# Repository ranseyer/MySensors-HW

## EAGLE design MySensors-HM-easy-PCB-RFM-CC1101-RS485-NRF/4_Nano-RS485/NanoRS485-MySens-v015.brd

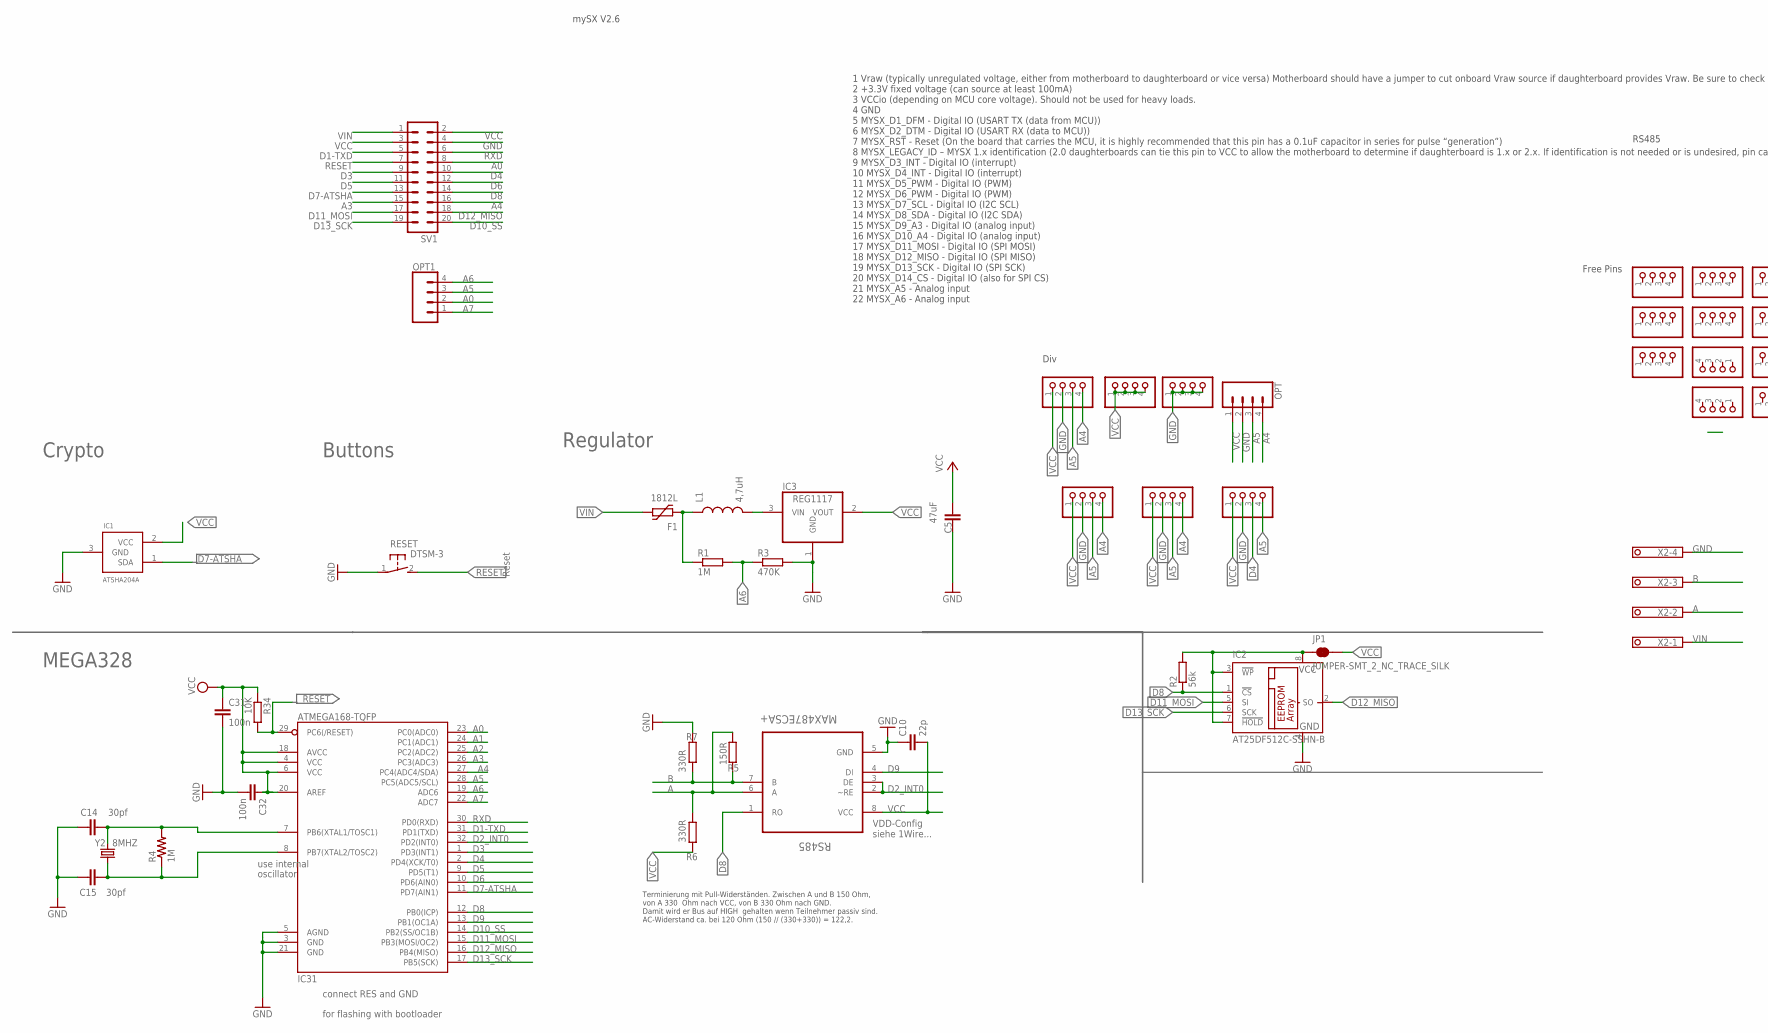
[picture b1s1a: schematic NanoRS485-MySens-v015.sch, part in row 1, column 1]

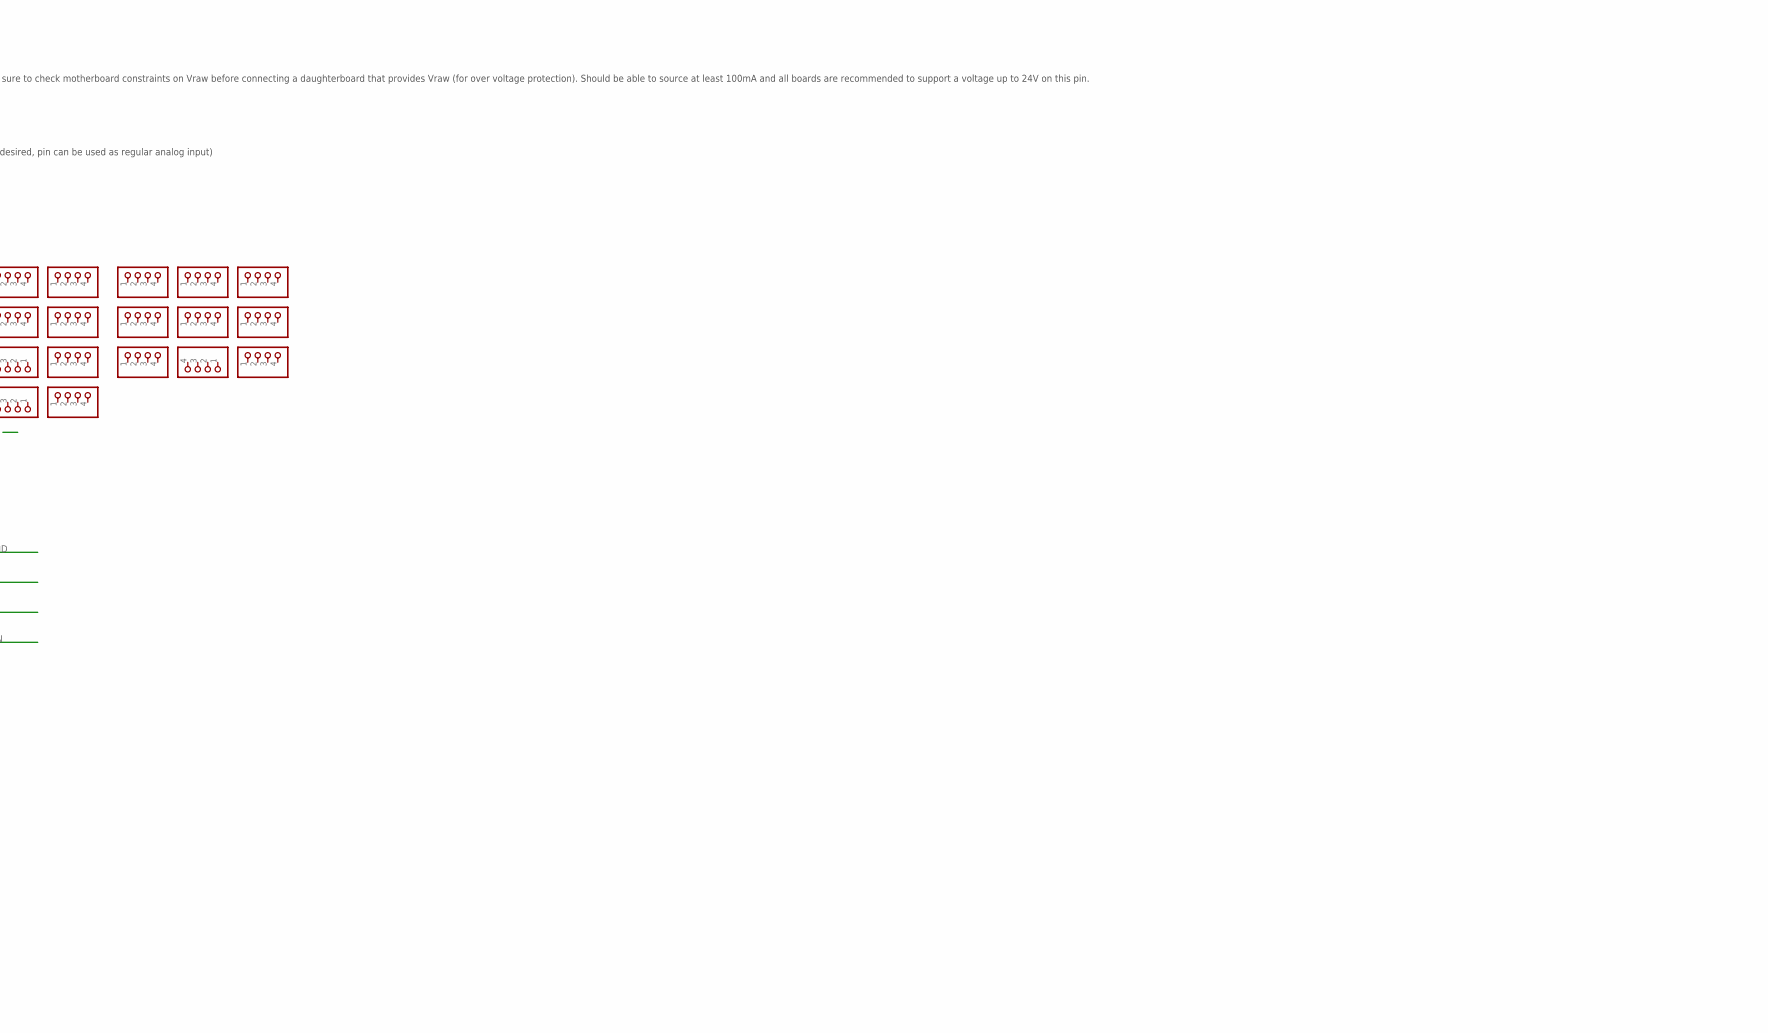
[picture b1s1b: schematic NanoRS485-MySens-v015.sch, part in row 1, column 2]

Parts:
BH1750: PINHD-1X04_2.54-S; 1X04-S
C5: 47uF; C1210
C10: 22p; C0805
C14, C15: 30pf; 0805
C31, C32: 100n; C0805
F1: 1812L
I2C-1, I2C-2: PINHD-1X04_2.54-S; 1X04-S
IC1: ATSHA204A; SOT23
IC2: AT25DF512C-SSHN-B; SO-08
IC3: REG1117; SOT223
IC31: ATMEGA168-TQFP; TQFP32-08
JP1: JUMPER-SMT_2_NC_TRACE_SILK; SMT-JUMPER_2_NC_TRACE_SILK
JP2, JP3, JP4, JP5, JP6, JP7, JP8, JP9, JP10, JP11, JP12, JP13, JP14, JP15, JP16, JP17, JP18, JP19, JP20, JP21, JP22, JP23: PINHD-1X04_2.54-S; 1X04-S
L1: 4,7uH; 0805
MOTION: PINHD-1X04_2.54-S; 1X04-S
OPT, OPT1: CONN_04; 1X04
R1: 1M; R0805
R2: 56k; M0805
R3: 470K; R0805
R4: 1M; 0805
R5: 150R; R0805
R6, R7: 330R; R0805
R34: 10K; R0805
RESET: DTSM-3
RS485: MAX487ECSA+; SOIC127P600X175-8N
SV1: MA10-2
X2: 1751264
Y2: 8MHZ; CRYSTAL-TXC-7A

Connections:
A: R5.1, R6.2, RS485.6 (A), X2.2
A0: IC31.23 (PC0(ADC0)), OPT1.2, SV1.8
A1: IC31.24 (PC1(ADC1))
A2: IC31.25 (PC2(ADC2))
A3: IC31.26 (PC3(ADC3)), SV1.15
A4: BH1750.4, I2C-1.4, I2C-2.4, IC31.27 (PC4(ADC4/SDA)), OPT.4, SV1.16
A5: BH1750.3, I2C-1.3, I2C-2.3, IC31.28 (PC5(ADC5/SCL)), MOTION.4, OPT.3, OPT1.3
A6: IC31.19 (ADC6), OPT1.4, R1.2, R3.1
A7: IC31.22 (ADC7), OPT1.1
B: R5.2, R7.1, RS485.7 (B), X2.3
D1-TXD: IC31.31 (PD1(TXD)), SV1.5
D2_INT0: IC31.32 (PD2(INT0)), RS485.2 (~RE), RS485.3 (DE)
D3: IC31.1 (PD3(INT1)), SV1.9
D4: IC31.2 (PD4(XCK/T0)), MOTION.3, SV1.10
D5: IC31.9 (PD5(T1)), SV1.11
D6: IC31.10 (PD6(AIN0)), SV1.12
D7-ATSHA: IC1.1 (SDA), IC31.11 (PD7(AIN1)), SV1.13
D8: IC2.1 (!CS), IC31.12 (PB0(ICP)), R2.1, RS485.1 (RO), SV1.14
D9: IC31.13 (PB1(OC1A)), RS485.4 (DI)
D10_SS: IC31.14 (PB2(SS/OC1B)), SV1.20
D11_MOSI: IC2.5 (SI), IC31.15 (PB3(MOSI/OC2)), SV1.17
D12_MISO: IC2.2 (SO), IC31.16 (PB4(MISO)), SV1.18
D13_SCK: IC2.6 (SCK), IC31.17 (PB5(SCK)), SV1.19
GND: BH1750.2, C5.1, C10.1, C14.1, C15.1, C31.2, C32.2, I2C-1.2, I2C-2.2, IC1.3 (GND), IC2.4 (GND), IC3.1 (GND), IC31.3 (GND), IC31.5 (AGND), IC31.21 (GND), JP2.1, JP2.2, JP2.3, JP2.4, MOTION.2, OPT.2, R3.2, R7.2, RESET.1, RS485.5 (GND), SV1.4, X2.4
unnamed: C14.2, IC31.7 (PB6(XTAL1/TOSC1)), R4.2, Y2.P$2 (2)
unnamed: C15.2, IC31.8 (PB7(XTAL2/TOSC2)), R4.1, Y2.P$1 (1)
RAW: IC3.3 (VIN), L1.2
RESET: IC31.29 (PC6(/RESET)), R34.2, RESET.2, SV1.7
RXD: IC31.30 (PD0(RXD)), SV1.6
VCC: BH1750.1, C5.2, C10.2, C31.1, C32.1, I2C-1.1, I2C-2.1, IC1.2 (VCC), IC3.2 (VOUT), IC31.4 (VCC), IC31.6 (VCC), IC31.18 (AVCC), IC31.20 (AREF), JP1.2, JP3.1, JP3.2, JP3.3, JP3.4, MOTION.1, OPT.1, R6.1, R34.1, RS485.8 (VCC), SV1.2, SV1.3
VCC1: IC2.3 (!WP), IC2.7 (!HOLD), IC2.8 (VCC), JP1.1, R2.2
VIN: F1.P$2 (2), SV1.1, X2.1
VIN-FUSED: F1.P$1 (1), L1.1, R1.1

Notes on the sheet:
MEGA328
use internal
oscillator
connect RES and GND
for flashing with bootloader
Reset
Crypto
Buttons
Regulator
RS485
VDD-Config siehe 1Wire...
Terminierung mit Pull-Widerständen. Zwischen A und B 150 Ohm, von A 330 Ohm nach VCC, von B 330 Ohm nach GND. Damit wird er Bus auf HIGH gehalten wenn Teilnehmer passiv sind. AC-Widerstand ca. bei 120 Ohm (150 // (330+330)) = 122,2.
1 Vraw (typically unregulated voltage, either from motherboard to daughterboard or vice versa) Motherboard should have a jumper to cut onboard Vraw source if daughterboard provides Vraw. Be sure to check motherboard constraints on Vraw before connecting a daughterboard that provides Vraw (for over 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
mySX V2.6
Div
Free Pins

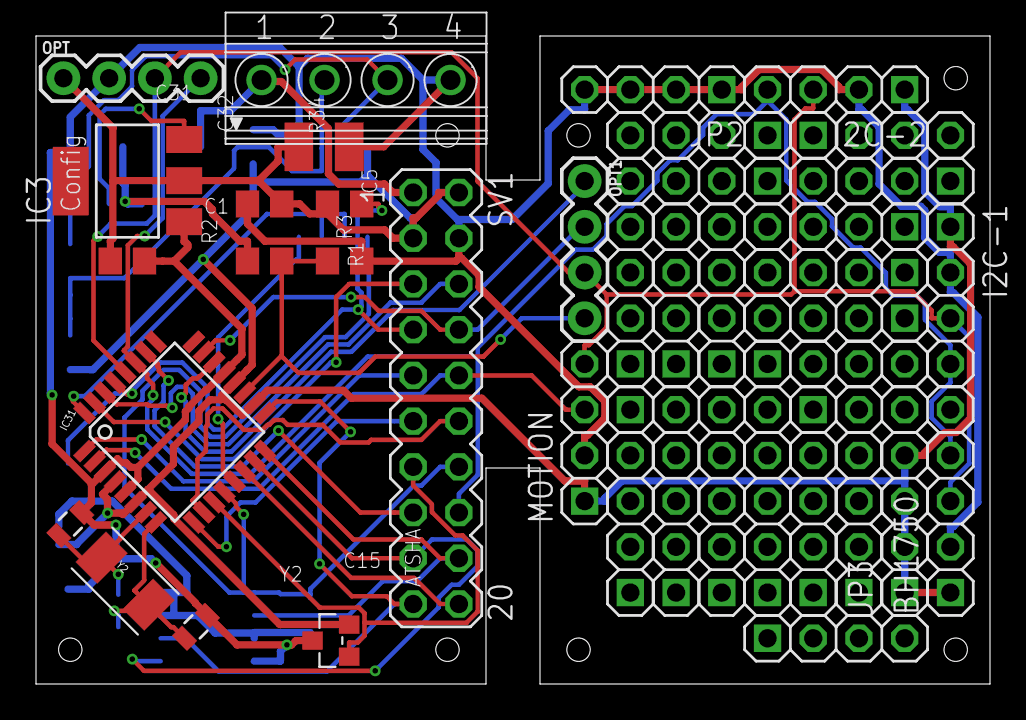
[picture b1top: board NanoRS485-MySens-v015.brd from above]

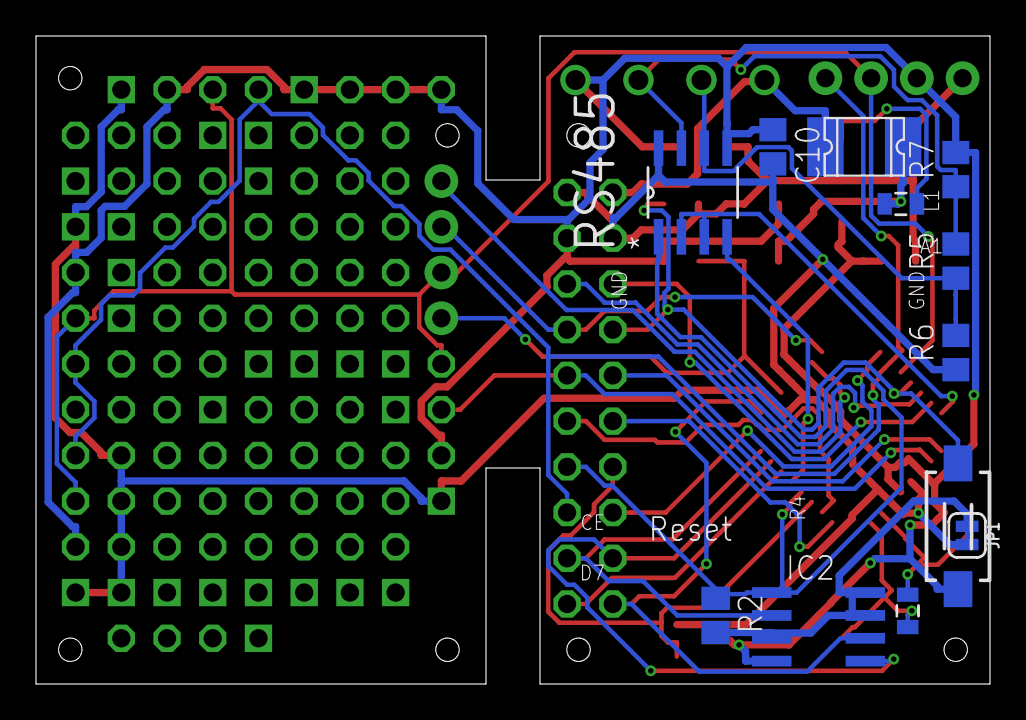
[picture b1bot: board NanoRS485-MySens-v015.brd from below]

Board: 2 copper layers, 53.0 x 36.0 mm, 54 parts (12 on the bottom side), 31 nets.

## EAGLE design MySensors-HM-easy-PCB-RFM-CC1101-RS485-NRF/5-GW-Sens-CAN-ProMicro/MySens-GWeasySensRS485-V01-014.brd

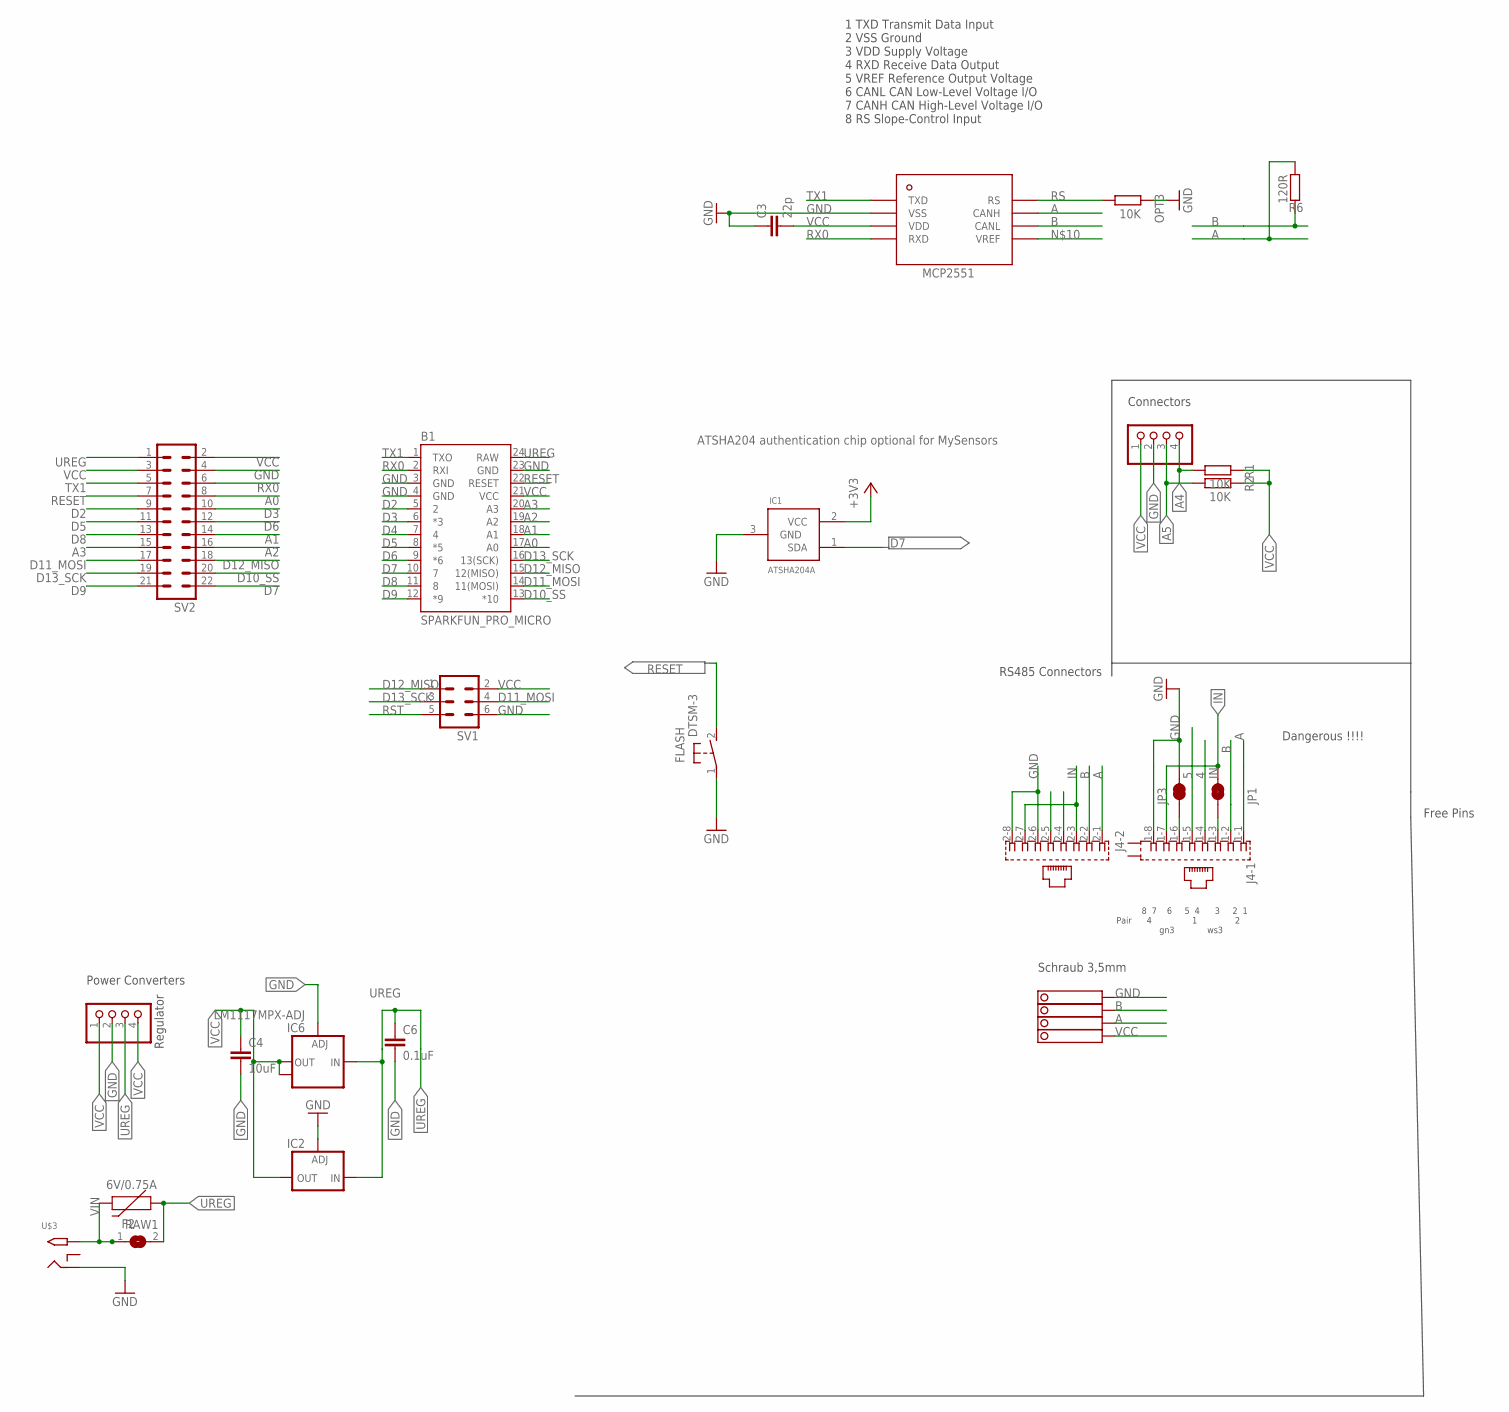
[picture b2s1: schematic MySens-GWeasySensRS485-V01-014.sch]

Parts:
B1: SPARKFUN_PRO_MICRO
C3: 22p; C0805
C4: 10uF; C1210
C6: 0.1uF; C1206
F2: 6V/0.75A; 1206
FLASH: DTSM-3
IC1: ATSHA204A; SOT23
IC2: LD117ADT50TR; DPACK
IC6: LM1117MPX-ADJ; SOT223
J4: RJ45_2X_NARROW_SHILDPINS_NOCASE
JP1, JP3: JUMPER-SMT_2_NC_TRACE_SILK; SMT-JUMPER_2_NC_TRACE_SILK
JP10: PINHD-1X04_2.54-S; 1X04-S
OPT3: 10K; R0805
R1, R2: 10K; R0805
R6: 120R; R0805
RAW1: SJ
STEPDWN: PINHD-1X04_2.54-S; 1X04-S
SV1: MA03-2
SV2: MA11-2
U$1: MCP2551; SOIC-8
U$3: 2.1MMJACKTHM; PJ-102A
X4: 1751264

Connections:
1: J4.1-3 (3), JP1.1
2: J4.1-6 (6), JP3.1
3V3: IC1.2 (VCC)
4: J4.1-4 (4)
5: J4.1-5 (5)
A: J4.1-1 (1), J4.2-1 (1), R6.1, U$1.CANH, X4.2
A0: B1.17 (A0), SV2.8
A1: B1.18 (A1), SV2.14
A2: B1.19 (A2), SV2.16
A3: B1.20 (A3), SV2.15
A4: JP10.4, R1.2
A5: JP10.3, R2.2
B: J4.1-2 (2), J4.2-2 (2), R6.2, U$1.CANL, X4.3
D2: B1.5 (2), SV2.9
D3: B1.6 (*3), SV2.10
D4: B1.7 (4)
D5: B1.8 (*5), SV2.11
D6: B1.9 (*6), SV2.12
D7: B1.10 (7), IC1.1 (SDA), SV2.22
D8: B1.11 (8), SV2.13
D9: B1.12 (*9), SV2.21
D10_SS: B1.13 (*10), SV2.20
D11_MOSI: B1.14 (11(MOSI)), SV1.4, SV2.17
D12_MISO: B1.15 (12(MISO)), SV1.1, SV2.18
D13_SCK: B1.16 (13(SCK)), SV1.3, SV2.19
GND: B1.3 (GND), B1.4 (GND), B1.23 (GND), C3.1, C4.2, C6.2, FLASH.1, IC1.3 (GND), IC2.1 (ADJ), IC6.1 (ADJ), J4.1-8 (8), J4.2-6 (6), J4.2-8 (8), JP3.2, JP10.2, OPT3.1, STEPDWN.2, SV1.6, SV2.4, U$1.VSS, U$3.RING, X4.4
IN: J4.1-7 (7), J4.2-3 (3), J4.2-7 (7), JP1.2
RESET: B1.22 (RESET), FLASH.2, SV2.7
RS: OPT3.2, U$1.RS
RST: SV1.5
RX0: B1.2 (RXI), SV2.6, U$1.RXD
TX1: B1.1 (TXO), SV2.5, U$1.TXD
UREG: B1.24 (RAW), C6.1, F2.1, IC2.3 (IN), IC6.3 (IN), RAW1.2, STEPDWN.3, SV2.1
VCC: B1.21 (VCC), C3.2, C4.1, IC2.4 (OUT), IC6.2 (OUT), IC6.TAB (OUT1), JP10.1, R1.1, R2.1, STEPDWN.1, STEPDWN.4, SV1.2, SV2.2, SV2.3, U$1.VDD, X4.1
VIN: F2.2, RAW1.1, U$3.TIP

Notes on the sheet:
Connectors
Free Pins
ATSHA204 authentication chip optional for MySensors
8 7 6 5 4 3 2 1 Pair 4 1 2 gn3 ws3
Dangerous !!!!
RS485 Connectors
Schraub 3,5mm
Power Converters
Regulator
1 TXD Transmit Data Input 2 VSS Ground 3 VDD Supply Voltage 4 RXD Receive Data Output 5 VREF Reference Output Voltage 6 CANL CAN Low-Level Voltage I/O 7 CANH CAN High-Level Voltage I/O 8 RS Slope-Control Input

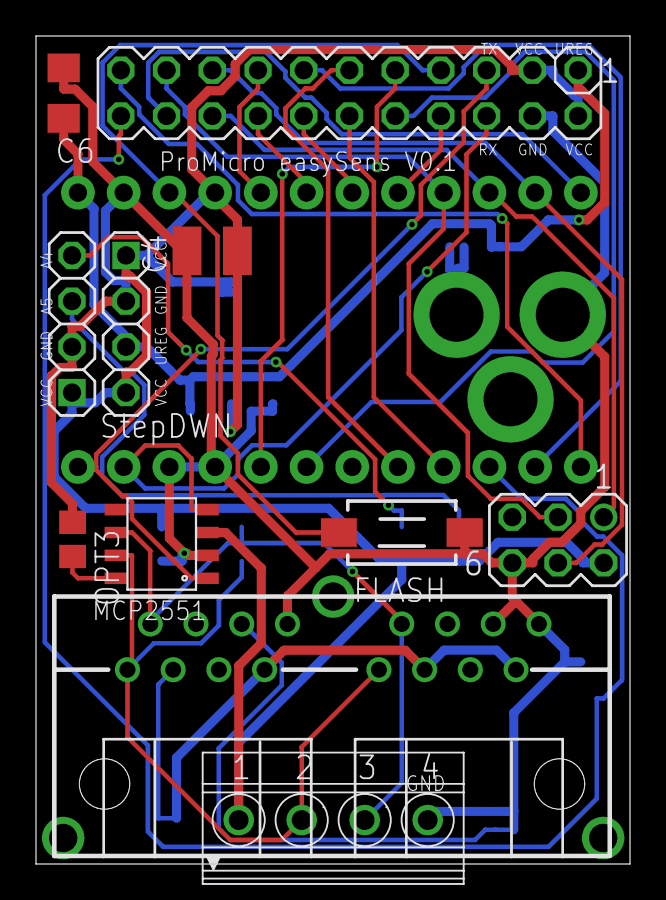
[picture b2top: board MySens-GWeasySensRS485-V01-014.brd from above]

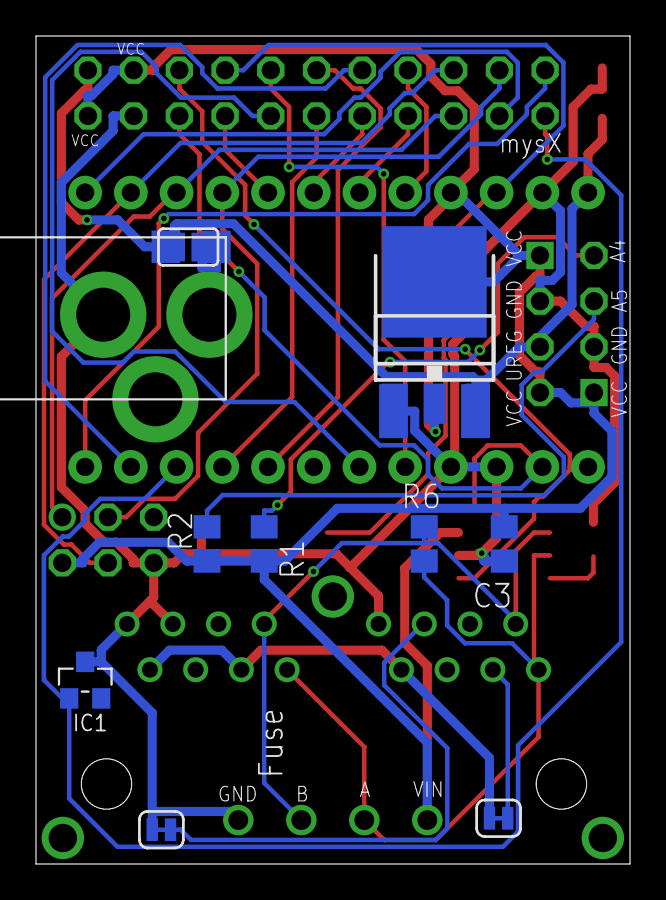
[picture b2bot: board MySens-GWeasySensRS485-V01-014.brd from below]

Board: 2 copper layers, 33.0 x 46.0 mm, 24 parts (12 on the bottom side), 30 nets.

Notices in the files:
parts and their libraries:
SparkFun-FreqCtrl: Licensing: Creative Commons ShareAlike 4.0 International - https://creativecommons.org/licenses/by-sa/4.0
SparkFun-Passives: Licensing: CC v3.0 Share-Alike You are welcome to use this library for commercial purposes.
